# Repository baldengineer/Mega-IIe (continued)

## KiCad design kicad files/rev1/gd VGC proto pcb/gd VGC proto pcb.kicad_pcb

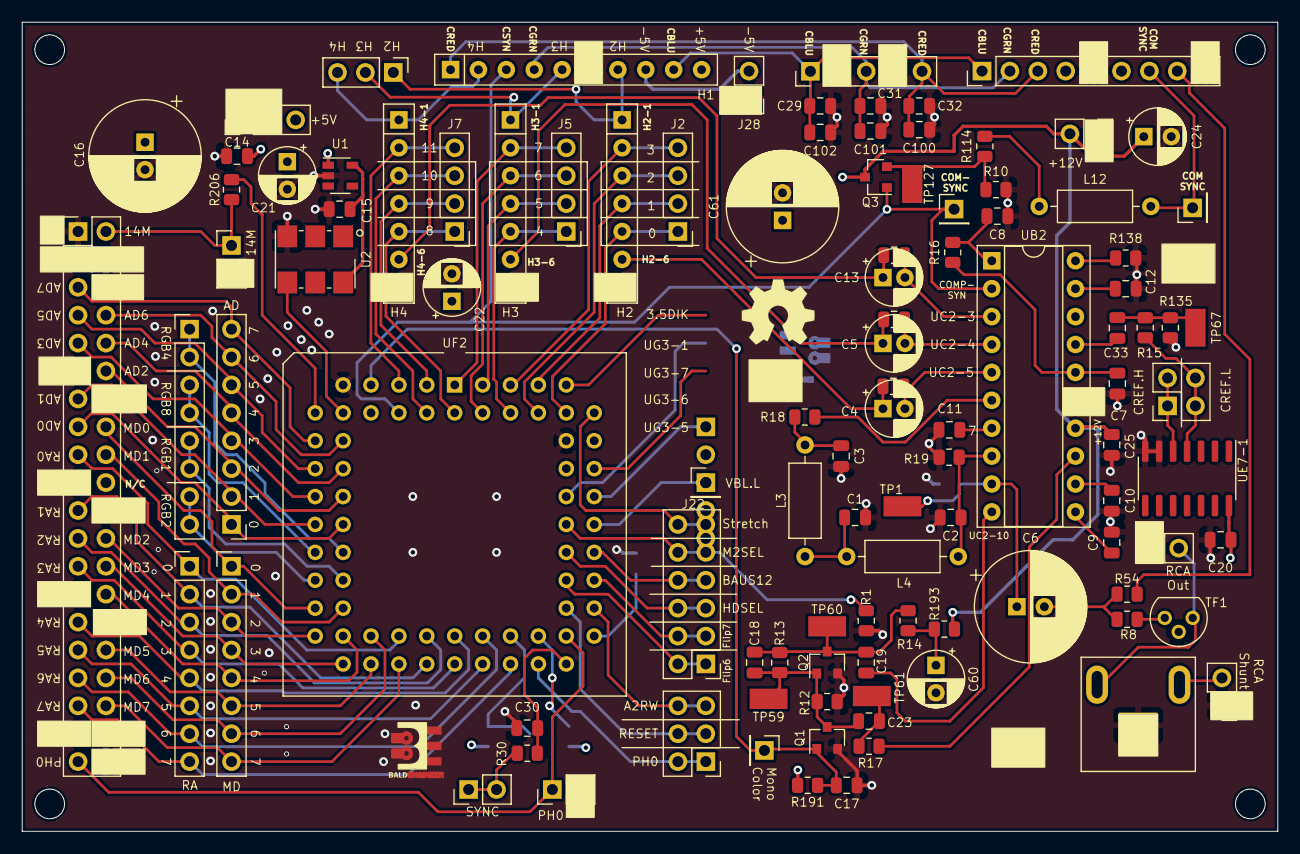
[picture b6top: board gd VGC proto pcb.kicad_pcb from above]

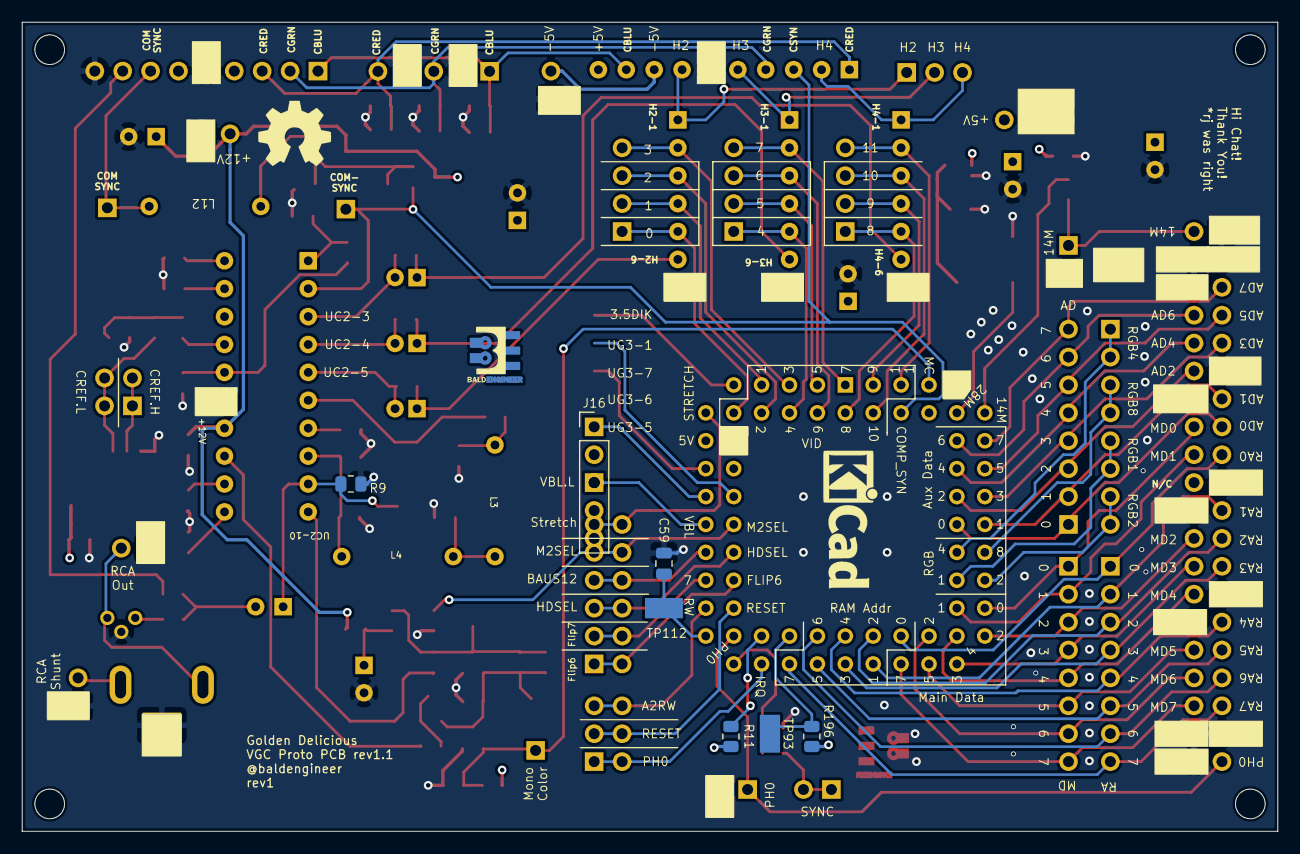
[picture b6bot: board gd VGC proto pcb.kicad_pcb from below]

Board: 4 copper layers, 114.3 x 73.7 mm, 123 parts (9 on the bottom side), 112 nets.

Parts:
C1, C23, C30: 56p; C_0805_2012Metric
C2, C3: 18p; C_0805_2012Metric
C4, C5, C13: 22uF; CP_Radial_D5.0mm_P2.00mm
C4alt1, C5alt1, C6alt1: 22uF; C_0805_2012Metric
C6: 1000u; CP_Radial_D10.0mm_P2.50mm
C7, C9, C10, C17: 0.1u; C_0805_2012Metric
C8: 1n; C_0805_2012Metric
C11, C12: 0.01u; C_0805_2012Metric
C14, C15: 1uF; C_0805_2012Metric
C16, C61: 470u; CP_Radial_D10.0mm_P2.50mm
C18: 27p; C_0805_2012Metric
C19: .001u; C_0805_2012Metric
C20: 100n; C_0805_2012Metric
C21, C22, C24: 10u; CP_Radial_D5.0mm_P2.50mm
C25, C59: 1u; C_0805_2012Metric
C29, C31, C32: 33p; C_0805_2012Metric
C33: 220p; C_0805_2012Metric
C60: 22u; CP_Radial_D5.0mm_P2.50mm
C100, C101, C102: 120p; C_0805_2012Metric
H1: Video_Sync; R_Array_SIP10
H2, H3, H4: VideoThingy; R_Array_SIP7
H5, H6, H7, H8: MountingHole; MountingHole_2.7mm_M2.5
J1: +5V_IN; PinHeader_1x03_P2.54mm_Vertical
J2: Video Binary B; PinHeader_1x04_P2.54mm_Vertical
J3: Aux Data Bus; PinHeader_1x08_P2.54mm_Vertical
J4: DAC RGB; PinHeader_1x03_P2.54mm_Vertical
J5: Video Binary G; PinHeader_1x04_P2.54mm_Vertical
J6: COMP_RGB; PinHeader_1x05_P2.54mm_Vertical
J7: Video Binary R; PinHeader_1x04_P2.54mm_Vertical
J8: RAM Addr Bus; PinHeader_1x08_P2.54mm_Vertical
J9: Composite Sync; PinHeader_1x01_P2.54mm_Vertical
J10: VID_OUT; PinHeader_1x09_P2.54mm_Vertical
J11: RCA MONO OUT; Jack_RCA_Switchcraft_PJRAN1X1UxxX
J12: Main Data Bus; PinHeader_1x08_P2.54mm_Vertical
J13: COMSYNC; PinHeader_1x01_P2.54mm_Vertical
J14: Mono-Color; PinHeader_1x01_P2.54mm_Vertical
J15: VBL; PinHeader_1x01_P2.54mm_Vertical
J16: RTC; PinHeader_1x05_P2.54mm_Vertical
J17: RCA Shunt Select; PinHeader_1x02_P2.54mm_Vertical
J18: RCA; PinHeader_1x02_P2.54mm_Vertical
J19: CREF; PinHeader_2x02_P2.54mm_Vertical
J20: RGB In; PinHeader_1x08_P2.54mm_Vertical
J21: CLK_14M; PinHeader_1x02_P2.54mm_Vertical
J22: Memory Control; PinHeader_2x06_P2.54mm_Vertical
J23: VGC Extra; PinHeader_2x03_P2.54mm_Vertical
J24: CLK_PH0; PinHeader_1x02_P2.54mm_Vertical
J25: Bald-Ext-1; PinHeader_2x20_P2.54mm_Vertical
J26: SYNC; PinHeader_1x02_P2.54mm_Vertical
J27: 12V_IN; PinHeader_1x02_P2.54mm_Vertical
J28: -5V_In; PinHeader_1x02_P2.54mm_Vertical
L3, L4: 10u; L_Axial_L6.6mm_D2.7mm_P10.16mm_Horizontal_Vishay_IM-2
L12: 1.5u; L_Axial_L6.6mm_D2.7mm_P10.16mm_Horizontal_Vishay_IM-2
Q1, Q2, Q3: BC817; SOT-23
R1: 0; R_0805_2012Metric
R8, R54, R206: 75; R_0805_2012Metric
R9, R12, R114: 220; R_0805_2012Metric
R10: 1.5K; R_0805_2012Metric
R11, R13, R14, R17, R30: 1k; R_0805_2012Metric
R15: 1.5k; R_0805_2012Metric
R16: 51k; R_0805_2012Metric
R18, R19, R135: 470; R_0805_2012Metric
R138, R193: 100; R_0805_2012Metric
R191, R196: 4.7k; R_0805_2012Metric
TF1: CapacitiveTransformer; TO-92
TP1, TP2, TP3, TP4, TP5, TP59, TP60, TP61, TP67, TP93, TP112, TP127: TestPoint; Harwin-S1751-46-Test-Point
U1: MIC5504-3.3YM5; SOT-23-5
U2: 28.636360 MHz; Oscillator_SMD_IDT_JU6-6_7.0x5.0mm_P2.54mm
UB2: MC1377; DIP-20_W7.62mm_Socket
UE7-1: 74LS02; SOIC-14_3.9x8.7mm_P1.27mm
UF2: VGC; PLCC-68_THT-Socket
svg2mod, svg2mod#2: G***; BE5v2

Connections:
+3V3: C15.1, U1.5, U2.6
+5V: C14.2, C16.1, C20.1, C21.1, C22.1, C61.1, H1.10, J1.3, R11.2, R191.1, R196.2, U1.1, UE7-1.14, UF2.8, UF2.58
+12V: C24.1, C25.2, J27.2, Q3.3, R193.2, UB2.14
-5V: H1.8, J28.2
/3.5DIK: J16.5, UF2.61
/14M.H: R206.1, UF2.10
/14MD.H: J21.1, J25.2, R206.2
/28M: U2.4, UF2.11
/A2R-W.H: J23.5, J23.6, UF2.46
/ADBUS0: J3.1, J25.15, UF2.19
/ADBUS1: J3.2, J25.13, UF2.18
/ADBUS2: J3.3, J25.12, UF2.17
/ADBUS3: J3.4, J25.9, UF2.16
/ADBUS4: J3.5, J25.10, UF2.15
/ADBUS5: J3.6, J25.7, UF2.14
/ADBUS6: J3.7, J25.8, UF2.13
/ADBUS7: J3.8, J25.5, UF2.12
/BABUS12: J22.7, J22.8, UF2.50
/COMP-BLUE: C29.1, C102.2, H1.9, J6.1, J10.1
/COMP-GREEN: C31.1, C101.2, H1.4, J6.3, J10.2
/COMP-RED: C32.1, C100.2, H1.1, J6.5, J10.3
/COMP-SYN: H1.3, J9.1, Q3.1, UB2.2, UF2.6
/COMSYNC: J10.7, J13.1, L12.2
/FLIP6.H: J22.1, J22.2, UF2.49
/FLIP7.H: J22.3, J22.4, UF2.48
/H2-1: H1.7, H2.1, J4.1
/H2-6: C4.1, C4alt1.2, H2.6
/H3-1: H1.5, H3.1, J4.2
/H3-6: C5.1, C5alt1.2, H3.6
/H4-1: H1.2, H4.1, J4.3
/H4-6: C6alt1.2, C13.1, H4.6
/HDSEL.H: J22.5, J22.6, UF2.51
/IRQ.L: J23.1, J23.2, UF2.41
/J11-1: J11.2, J18.2, TF1.1
/L3-1: C3.1, L3.1, R18.2
/L4-1: C1.1, L3.2, L4.1
/M2SEL.L: J22.9, J22.10, R1.1, UF2.53
/MDBUS0: J12.1, J25.16, UF2.24
/MDBUS1: J12.2, J25.18, UF2.25
/MDBUS2: J12.3, J25.24, UF2.26
/MDBUS3: J12.4, J25.26, UF2.27
/MDBUS4: J12.5, J25.28, UF2.28
/MDBUS5: J12.6, J25.32, UF2.29
/MDBUS6: J12.7, J25.34, UF2.30
/MDBUS7: J12.8, J25.36, UF2.31
/MONO-COLOR: C17.2, J14.1, Q1.1, R191.2, UF2.7
/PH0.H: J24.1, J25.39, UF2.45
/Q2-3: C18.1, C19.2, Q2.3, R13.1, R14.2, TP60.1
/R8-2: R8.2, TF1.3
/R13-1: C18.2, C23.2, Q1.3, Q2.1, R12.1, R13.2, TP59.1
/R14-2: C60.1, R14.1, R193.1
/R17-1: C23.1, R17.1, TP61.1
/R54-1: C6.2, R8.1, R54.1
/R54-2: J10.8, R54.2
/R114-1: Q3.2, R10.1, R114.1, TP127.1
/R114-2: L12.1, R114.2
/R135-1: C33.1, R15.1, R135.1, TP67.1
/RABUS0: J8.1, J25.17, UF2.32
/RABUS1: J8.2, J25.21, UF2.33
/RABUS2: J8.3, J25.23, UF2.34
/RABUS3: J8.4, J25.25, UF2.35
/RABUS4: J8.5, J25.29, UF2.36
/RABUS5: J8.6, J25.31, UF2.37
/RABUS6: J8.7, J25.33, UF2.38
/RABUS7: J8.8, J25.35, UF2.39
/RESET.L: J23.3, J23.4, UF2.47
/RGB1.H: J20.5, J20.6, UF2.23
/RGB2.H: J20.7, J20.8, UF2.22
/RGB4.H: J20.1, J20.2, UF2.21
/RGB8.H: J20.3, J20.4, UF2.20
/STRETCH.L: J22.11, J22.12, UF2.60
/SYNC.L: J26.1, J26.2, R30.2
/U18TEST: R11.1, UF2.42
/UC2-3: C6alt1.1, C13.2, UB2.3
/UC2-4: C5.2, C5alt1.1, UB2.4
/UC2-5: C4.2, C4alt1.1, UB2.5
/UC2-6: R18.1, UB2.6
/UC2-7: C11.1, UB2.7
/UC2-8: C2.1, L4.2, R19.2, UB2.8
/UC2-9: C6.1, R9.2, TP1.1, UB2.9
/UC2-10: C19.1, UB2.10
/UC2-11: C9.1, UB2.11
/UC2-12: C10.1, UB2.12
/UC2-13: R17.2, UB2.13
/UC2-16: C7.1, R16.1, UB2.16
/UC2-17: C33.2, UB2.17
/UC2-19: C12.1, UB2.19
/UC2-20: R138.2, UB2.20
/UG3-1: J16.4, UF2.55
/UG3-5: J16.1, UF2.54
/UG3-7: J16.3, UF2.56
/UH2-40: R196.1, TP93.1, UF2.40
/UH2-43: C30.2, R30.1, UF2.43
/UH2-44: C59.1, TP112.1, UF2.44
/VBL.L: J15.1, UF2.52
/VID0: H2.5, J2.1, UF2.62
/VID1: H2.4, J2.2, UF2.63
/VID2: H2.3, J2.3, UF2.64
/VID3: H2.2, J2.4, UF2.65
/VID4: H3.5, J5.1, UF2.66
/VID5: H3.4, J5.2, UF2.67
/VID6: H3.3, J5.3, UF2.68
/VID7: H3.2, J5.4, UF2.1
/VID8: H4.5, J7.1, UF2.2
/VID9: H4.4, J7.2, UF2.3
/VID10: H4.3, J7.3, UF2.4
/VID11: H4.2, J7.4, UF2.5
CREF.H: J19.1, J19.2, UE7-1.5
CREF.L: J19.3, J19.4, R15.2, UE7-1.4
GND: C1.2, C2.2, C3.2, C7.2, C8.1, C9.2, C10.2, C11.2, C12.2, C14.1, C15.2, C16.2, C17.1, C20.2, C21.2, C22.2, C24.2, C25.1, C29.2, C30.1, C31.2, C32.2, C59.2, C60.2, C61.2, C100.1, C101.1, C102.1, H1.6, H2.7, H3.7, H4.7, J1.1, J1.2, J6.2, J6.4, J10.5, J10.9, J11.1, J17.1, J18.1, J21.2, J24.2, J25.1, J25.3, J25.4, J25.6, J25.11, J25.14, J25.19, J25.22, J25.27, J25.30, J25.37, J25.38, J25.40, J27.1, J28.1, Q1.2, Q2.2, R1.2, R9.1, R10.2, R12.2, R19.1, R135.2, R138.1, TF1.2, TP2.1, TP3.1, TP4.1, TP5.1, U1.2, U2.3, UB2.15, UE7-1.6, UE7-1.7, UF2.9, UF2.59
unnamed: C8.2, R16.2, UB2.1
unnamed: J11.3, J17.2

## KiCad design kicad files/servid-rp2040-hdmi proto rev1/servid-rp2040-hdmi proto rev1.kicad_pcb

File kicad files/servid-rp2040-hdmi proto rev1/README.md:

# Apple II SERVID to HDMI Adapter Prototype
Board takes in the video signals from a MEGA-II and (hopefully) outputs HDMI.

Totally untested.

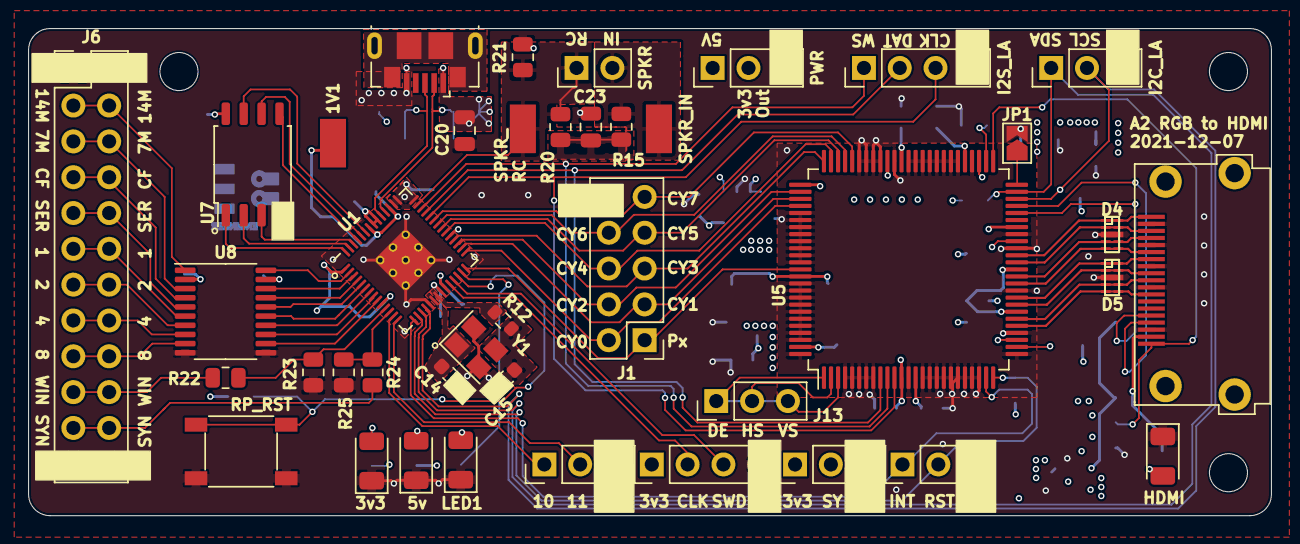
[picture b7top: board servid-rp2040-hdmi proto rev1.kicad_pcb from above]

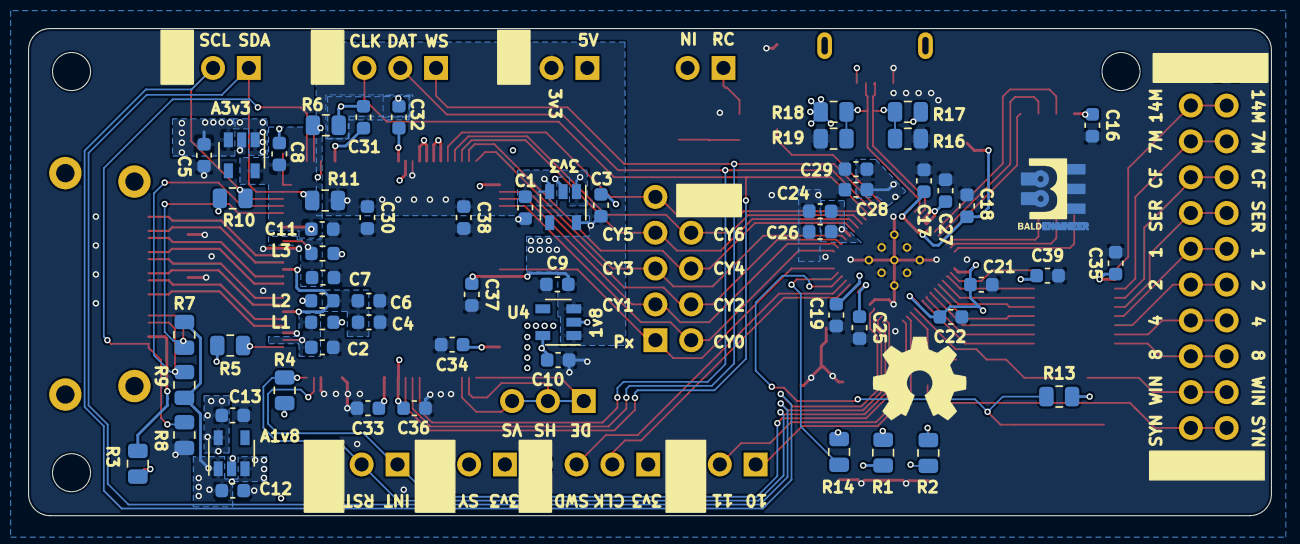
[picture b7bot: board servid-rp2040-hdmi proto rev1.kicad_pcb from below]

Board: 4 copper layers, 88.1 x 34.5 mm, 104 parts (60 on the bottom side), 88 nets.

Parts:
C1, C5, C9, C12, C19, C21, C35, C39: 1u; C_0603_1608Metric
C2, C3, C4, C6, C7, C8, C10, C11, C13, C16, C17, C18, C22, C24, C25, C26, C27, C28, C29, C30, C31, C32, C33, C34, C36, C37, C38: 100n; C_0603_1608Metric
C14, C15: 27p; C_0603_1608Metric
C20: 10u; C_0805_2012Metric
C23: 100n; C_0805_2012Metric
D1: 5v; LED_1206_3216Metric
D2: 3v3; LED_1206_3216Metric
D3: HDMI; LED_1206_3216Metric
D4, D5: RClamp0524P; SLP2510P8
D6: LED1; LED_1206_3216Metric
H1, H3, H4: MountingHole; MountingHole_2.7mm_M2.5
J1: ITU-656; PinHeader_2x05_P2.54mm_Vertical
J2: INT_LA; PinHeader_1x03_P2.54mm_Vertical
J3: I2C_LA; PinHeader_1x03_P2.54mm_Vertical
J4: I2S_LA; PinHeader_1x04_P2.54mm_Vertical
J5: USB_B_Micro-CHECK FOOTPRINT; USB_Micro-B_GCT_USB3076-30-A
J6: VIDS; PinHeader_2x12_P2.54mm_Vertical
J7: 10029449-111RLF; 10029449
J8: SWD; PinHeader_1x04_P2.54mm_Vertical
J9: GPIO; PinHeader_1x03_P2.54mm_Vertical
J10, J13: SYNCs; PinHeader_1x03_P2.54mm_Vertical
J11: SPKR; PinHeader_1x02_P2.54mm_Vertical
J12: PWR; PinHeader_1x03_P2.54mm_Vertical
JP1: PCADR; SolderJumper-2_P1.3mm_Open_TrianglePad1.0x1.5mm
L1, L2, L3: MPZ1608S221A; L_0603_1608Metric
R1, R2, R3, R14, R20: 470; R_0805_2012Metric
R4, R7, R8, R9, R10, R11, R13: 4k7; R_0805_2012Metric
R5: 698; R_0805_2012Metric
R6, R21: 1k; R_0805_2012Metric
R12: 1k; R_0603_1608Metric
R15: 100; R_0805_2012Metric
R16, R18: 75k; R_0805_2012Metric
R17, R19: 49.9k; R_0805_2012Metric
R22, R24: 22k; R_0805_2012Metric
R23, R25: 47k; R_0805_2012Metric
SW1: RP_RST; SW_Push_CK_PTS525_SM15
TP1: TP_1v1; Harwin-S1751-46-Test-Point
TP2: TP_SPKR_IN; Harwin-S1751-46-Test-Point
TP4: TP_SPKR_RC; Harwin-S1751-46-Test-Point
U1: RP2040; RP2040-QFN-56
U2, U3: MIC5504-3.3YM5; SOT-23-5
U4, U6: MIC5504-1.8YM5; SOT-23-5
U5: IT6613; LQFP-100_14x14mm_P0.5mm
U7: W25Q128JVS; SOIC-8_5.23x5.23mm_P1.27mm
U8: TXB0108PW; TSSOP-20_4.4x6.5mm_P0.65mm
Y1: ECS-120-18-33-JEM; Crystal_SMD_3225-4Pin_3.2x2.5mm
svg2mod: G***; BE5v2

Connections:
+1V1: C17.1, C18.1, C19.1, TP1.1, U1.23, U1.45, U1.50
+1V8: C10.1, C31.1, C32.1, C34.1, C36.1, U4.5, U5.12, U5.55, U5.64, U5.76, U5.99
+3V3: C3.1, C9.1, C16.1, C21.1, C22.1, C24.1, C25.1, C26.1, C27.1, C28.1, C29.1, C30.1, C33.1, C37.1, C38.1, C39.1, J8.1, J10.1, J12.2, R2.1, R4.1, R10.1, R11.1, R13.2, U1.1, U1.10, U1.22, U1.33, U1.42, U1.43, U1.44, U1.48, U1.49, U2.5, U4.1, U4.3, U5.14, U5.53, U5.66, U5.89, U7.8, U8.19
+5V: C1.1, C5.1, C12.1, C20.1, C35.1, J5.1, J12.1, R1.1, R7.1, R9.1, R16.1, R18.1, U2.1, U2.3, U3.1, U3.3, U6.1, U6.3, U8.2
/7M: J6.5, J6.6, U8.3
/14M: J6.3, J6.4, U8.1
/A1v8: C13.1, L1.1, L2.1, L3.1, R5.2, U6.5
/A3v3: C8.1, C11.1, U3.5, U5.44
/AVCC18: C4.1, C6.1, L2.2, U5.32, U5.38
/CREF: J6.7, J6.8, U8.4
/CY0: J1.2, U1.29, U5.79
/CY1: J1.3, U1.30, U5.78
/CY2: J1.4, U1.31, U5.77
/CY3: J1.5, U1.32, U5.75
/CY4: J1.6, U1.34, U5.74
/CY5: J1.7, U1.35, U5.73
/CY6: J1.8, U1.36, U5.72
/CY7: J1.9, U1.37, U5.71
/DDC_SCL: J7.15, R7.2, U5.46
/DDC_SDA: J7.16, R9.2, U5.47
/DE: J13.1, U5.1
/GPIO10: J9.1, U1.13
/GPIO11: J9.2, U1.14
/HDMI_5V: J7.18, R3.1
/HPD: J7.19, R8.2, U5.51
/HSYNC: J13.2, U5.2
/I2C_SCL: J3.2, R10.2, U1.18, U5.48
/I2C_SDA: J3.1, R11.2, U1.17, U5.49
/INT#: J2.1, U1.15, U5.24
/IT_RST#: J2.2, R4.2, U1.16, U5.25
/LED1: R14.1, U1.27
/PCADR: JP1.1, U5.50
/PIO_I2S_CLK: J4.3, U1.38, U5.11
/PIO_I2S_DATA: J4.2, U1.39, U5.9
/PIO_I2S_WS: J4.1, U1.40, U5.10
/PVCC1: C2.1, L1.2, U5.28
/PVCC2: C7.1, L3.2, U5.42
/PxCLK: J1.1, U1.28, U5.88
/QSPI_SCLK: U1.52, U7.6
/QSPI_SD0: U1.53, U7.5
/QSPI_SD1: U1.55, U7.2
/QSPI_SD2: U1.54, U7.3
/QSPI_SD3: U1.51, U7.7
/QSPI_SS: U1.56, U7.1
/RGB1: J6.11, J6.12, U8.6
/RGB2: J6.13, J6.14, U8.7
/RGB4: J6.15, J6.16, U8.8
/RGB8: J6.17, J6.18, U8.9
/Run: R13.1, SW1.2, U1.26
/SERVID: J6.9, J6.10, U8.5
/SPKR_IN: J11.2, R15.1, TP2.1
/SPKR_RC: J11.1, R20.1, R21.1, TP4.1, U1.41
/SWCLK: J8.2, U1.24
/SWD: J8.3, U1.25
/TMDS_CLK+: D5.4, D5.7, J7.10, U5.31
/TMDS_CLK-: D5.5, D5.6, J7.12, U5.30
/TMDS_D0+: D5.1, D5.10, J7.7, U5.34
/TMDS_D0-: D5.2, D5.9, J7.9, U5.33
/TMDS_D1+: D4.4, D4.7, J7.4, U5.37
/TMDS_D1-: D4.5, D4.6, J7.6, U5.36
/TMDS_D2+: D4.1, D4.10, J7.1, U5.40
/TMDS_D2-: D4.2, D4.9, J7.3, U5.39
/USB_DM: J5.2, R18.2, R19.1, U1.46
/USB_DP: J5.3, R16.2, R17.1, U1.47
/VSYNC: J13.3, U5.3
/XIN: C14.1, U1.20, Y1.1
/XOUT: R12.2, U1.21
/b7M: U1.3, U8.18
/b14M: U1.2, U8.20
/bCREF: U1.4, U8.17
/bRGB1: U1.6, U8.15
/bRGB2: U1.7, U8.14
/bRGB4: U1.8, U8.13
/bRGB8: U1.9, U8.12
/bSERVID: U1.5, U8.16
/~SYNC: J6.21, J6.22, R24.1
/~WINDOW: J6.19, J6.20, R22.1
/~bSYNC: R24.2, R25.1, U1.12
/~bWINDOW: R22.2, R23.1, U1.11
GND: C1.2, C2.2, C3.2, C4.2, C5.2, C6.2, C7.2, C8.2, C9.2, C10.2, C11.2, C12.2, C13.2, C14.2, C15.2, C16.2, C17.2, C18.2, C19.2, C20.2, C21.2, C22.2, C23.2, C24.2, C25.2, C26.2, C27.2, C28.2, C29.2, C30.2, C31.2, C32.2, C33.2, C34.2, C35.2, C36.2, C37.2, C38.2, C39.2, D1.1, D2.1, D3.1, D4.3, D4.8, D5.3, D5.8, D6.1, J1.10, J2.3, J3.3, J4.4, J5.5, J6.1, J6.2, J6.23, J6.24, J7.2, J7.5, J7.8, J7.11, J7.17, J8.4, J9.3, J10.3, J12.3, JP1.2, R6.1, R8.1, R17.2, R19.2, R21.2, R23.2, R25.2, SW1.1, U1.19, U1.57, U2.2, U3.2, U4.2, U5.4, U5.5, U5.6, U5.7, U5.8, U5.13, U5.15, U5.16, U5.17, U5.18, U5.19, U5.20, U5.21, U5.22, U5.23, U5.26, U5.29, U5.35, U5.41, U5.43, U5.54, U5.56, U5.57, U5.58, U5.59, U5.60, U5.61, U5.62, U5.63, U5.65, U5.67, U5.68, U5.69, U5.70, U5.80, U5.81, U5.82, U5.83, U5.84, U5.85, U5.86, U5.87, U5.90, U5.91, U5.92, U5.93, U5.94, U5.95, U5.96, U5.97, U5.98, U5.100, U6.2, U7.4, U8.10, U8.11, Y1.2, Y1.4
unnamed: C15.1, R12.1, Y1.3
unnamed: C23.1, R15.2, R20.2
unnamed: D1.2, R1.2
unnamed: D2.2, R2.2
unnamed: D3.2, R3.2
unnamed: D6.2, R14.2
unnamed: R5.1, U5.27
unnamed: R6.2, U5.52
